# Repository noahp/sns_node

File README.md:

sns_node
=====
Wireless sensor node system, comprised of 3(+1) components:  
* Sensor Node (2.4GHz low power radios)
* Network Monitor (network interface)
* Internet Bridge (user interface)
* (Repeater, optional, range extender)  

parts
=====
node micro
-----
[mouser part MKL02Z8](http://www.mouser.com/ProductDetail/Freescale-Semiconductor/MKL02Z8VFG4/?qs=sGAEpiMZZMttKWgNLnZcJr8OOhcQcoey)  
[datasheet](http://cache.freescale.com/files/32bit/doc/data_sheet/KL02P32M48SF0.pdf?fpsp=1&WT_TYPE=Data%20Sheets&WT_VENDOR=FREESCALE&WT_FILE_FORMAT=pdf&WT_ASSET=Documentation)  
[ref manual](http://cache.freescale.com/files/32bit/doc/ref_manual/KL02P32M48SF0RM.pdf?fpsp=1&WT_TYPE=Reference%20Manuals&WT_VENDOR=FREESCALE&WT_FILE_FORMAT=pdf&WT_ASSET=Documentation)

network monitor micro
-----
[mouser part MKL26Z256](http://www.mouser.com/ProductDetail/Freescale-Semiconductor/MKL26Z256VLH4/?qs=sGAEpiMZZMuoKKEcg8mMKEd509BQpO5pxz18L1jeLNc%3d)  
[datasheet](http://cache.freescale.com/files/microcontrollers/doc/data_sheet/KL26P121M48SF4.pdf)  
[ref manual](http://cache.freescale.com/files/microcontrollers/doc/ref_manual/KL26P121M48SF4RM.pdf)

power
-----
[low power lps](http://www.mouser.com/ProductDetail/Microchip-Technology/MCP1640T-I-CHY/?qs=sGAEpiMZZMsnDbBzJh6VGDDeXjwaXPWp)  
[inductor 4.7uH](http://www.mouser.com/ProductDetail/Sumida/CDRH4D18CNP-100PC/?qs=sGAEpiMZZMsg%252by3WlYCkUxi3fTgkZ6yAbP1KOW9D5Zs%3d)  
[battery holder AA](http://www.mouser.com/ProductDetail/Eagle-Plastic-Devices/12BH311A-GR/?qs=sGAEpiMZZMupuRtfu7GC%252bWdR22xe%2fSxxWAb7Knacbvo%3d)  
[battery holder AAA](http://www.mouser.com/ProductDetail/Eagle-Plastic-Devices/12BH412-GR/?qs=sGAEpiMZZMupuRtfu7GC%252basqiiwPG6fox5Hf9LOGvms%3d)  
[ldo 3.3v](http://www.mouser.com/ProductDetail/Skyworks-Solutions-Inc/AAT3220IGY-33-T1/?qs=sGAEpiMZZMsGz1a6aV8DcBc9KxeEYlaawDtM6jF3HEw%3d), [datasheet](http://www.mouser.com/ds/2/472/202250A-258357.pdf)  
usb connector
-----
[micro b](http://www.mouser.com/ProductDetail/FCI/10118192-0001LF/?qs=sGAEpiMZZMulM8LPOQ%252byk2%252bTbV8%2f2X5vivRX5xKgOBI%3d)
temp/humidity sensor
-----
[silabs](http://www.mouser.com/ProductDetail/Silicon-Labs/Si7020-A10-GM/?qs=sGAEpiMZZMvcRsgoMFfeP68xdtgWCbZByF2TKLTitEk%3d), [datasheet](http://www.silabs.com/Support%20Documents/TechnicalDocs/Si7020.pdf)

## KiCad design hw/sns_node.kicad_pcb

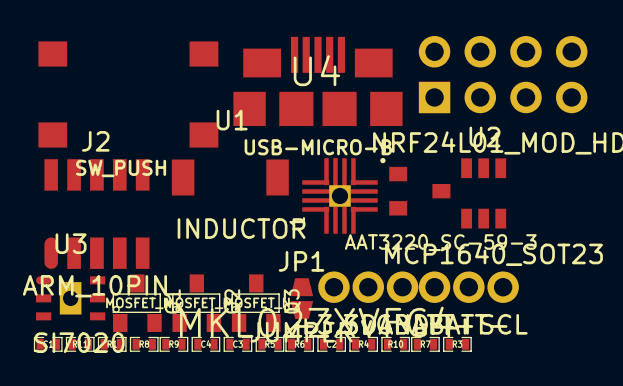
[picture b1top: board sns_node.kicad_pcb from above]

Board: 2 copper layers, 33 parts (0 on the bottom side), 22 nets, no tracks yet.

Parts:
C1: 4.7uF; SM0402
C2: 10uF; SM0402
C3, C4: 1uF; SM0402
J1: USB-MICRO-B; usb_micro_b_smt
J2: ARM_10PIN; ARM_10_PIN_SMT
JP1: JUMPER; jmp_small
P1: BATT-; TEST_0.100
P2: BATT+; TEST_0.100
P3: +3.3v; TEST_0.100
P4: SCL; TEST_0.100
P5: GND; TEST_0.100
P6: SDA; TEST_0.100
Q1, Q3: MOSFET_N; SOT23
Q2: MOSFET_P; SOT23
R1, R3, R10, R11: 3M; SM0402
R4: 1M; SM0402
R5: 1.3M; SM0402
R6: 240K; SM0402
R7: 510K; SM0402
R8, R9: 100K; SM0402
SW1: SW_PUSH; spst_pushbutton_smd
U1: INDUCTOR; CDRH4D18C_inductor
U2: MCP1640_SOT23; MCP1640
U3: SI7020; si7020_dfn6
U4: MKL02ZXVFG4; MKL02_QFN16
U5: AAT3220_SC-59-3; sc59
U6: NRF24L01_MOD_HDR; nrf24_8pin

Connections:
ACC_PWR: JP1.2, P3.1, U3.5
ACC_PWR_CTRL: JP1.1, R3.1, U4.11
BATT+: C1.1, P2.1, R4.1, U1.2, U2.6
CSN: U4.5, U6.4
EN: R4.2, U2.3
EN_CTRL: R1.1, U4.13
GND: C1.2, C2.2, C3.2, C4.2, J1.5, J1.6, J2.3, J2.5, J2.9, P5.1, R1.2, R3.2, R7.2, R10.2, SW1.2, U2.2, U3.2, U4.2, U5.1, U6.1
IRQ: U4.9, U6.8
MISO: U4.6, U6.7
MOSI: U4.7, U6.6
unnamed: C4.1, J1.1, U5.3
unnamed: R5.2, R6.1, U2.4
unnamed: U1.1, U2.1
RESET_b: J2.10, U4.15
SCK: U4.8, U6.5
SCL: P4.1, R8.2, U3.6, U4.4
SDA: P6.1, R9.2, U3.1, U4.3
SWD_CLK: J2.4, U4.14
SWD_IO: J2.2, U4.16
SWITCH/VBUS_SNS: R11.2, SW1.1, U4.10
VCC: C2.1, C3.1, J2.1, R5.1, R8.1, R9.1, R11.1, U2.5, U4.1, U5.2
VFB_SNS: R6.2, R7.1, U4.12

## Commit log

2014-02-18 - add kicadlib
2014-02-18 - add project files
2014-02-18 - add power supply
2014-02-18 - add pfet to control en signal
2014-02-18 - add system diagram
2014-02-18 - don't need svg eh
2014-02-20 - fix some typos
2014-02-20 - add header for 24l01
2014-02-20 - add nrf pwr control
2014-02-20 - add voltage sns circuit, connected to on chip comparator.
2014-02-20 - schematic done, add net list
2014-02-20 - add usb voltage supply + ldo
2014-02-23 - possible circuit to provide momentary turn on when battery is connected
2014-02-25 - add header for connecting i2c daughter boards - add acc_pwr fet
2014-02-27 - remove power-on circuit, pullup OK because IO keeps state during micro sleep.
2014-03-08 - new kicadlib, associations.
2014-03-18 - associate modules with footprints.
2014-04-21 - change vbus sns to share vfb_sns pin. add pdf.
2014-04-24 - update schematic and place comps
